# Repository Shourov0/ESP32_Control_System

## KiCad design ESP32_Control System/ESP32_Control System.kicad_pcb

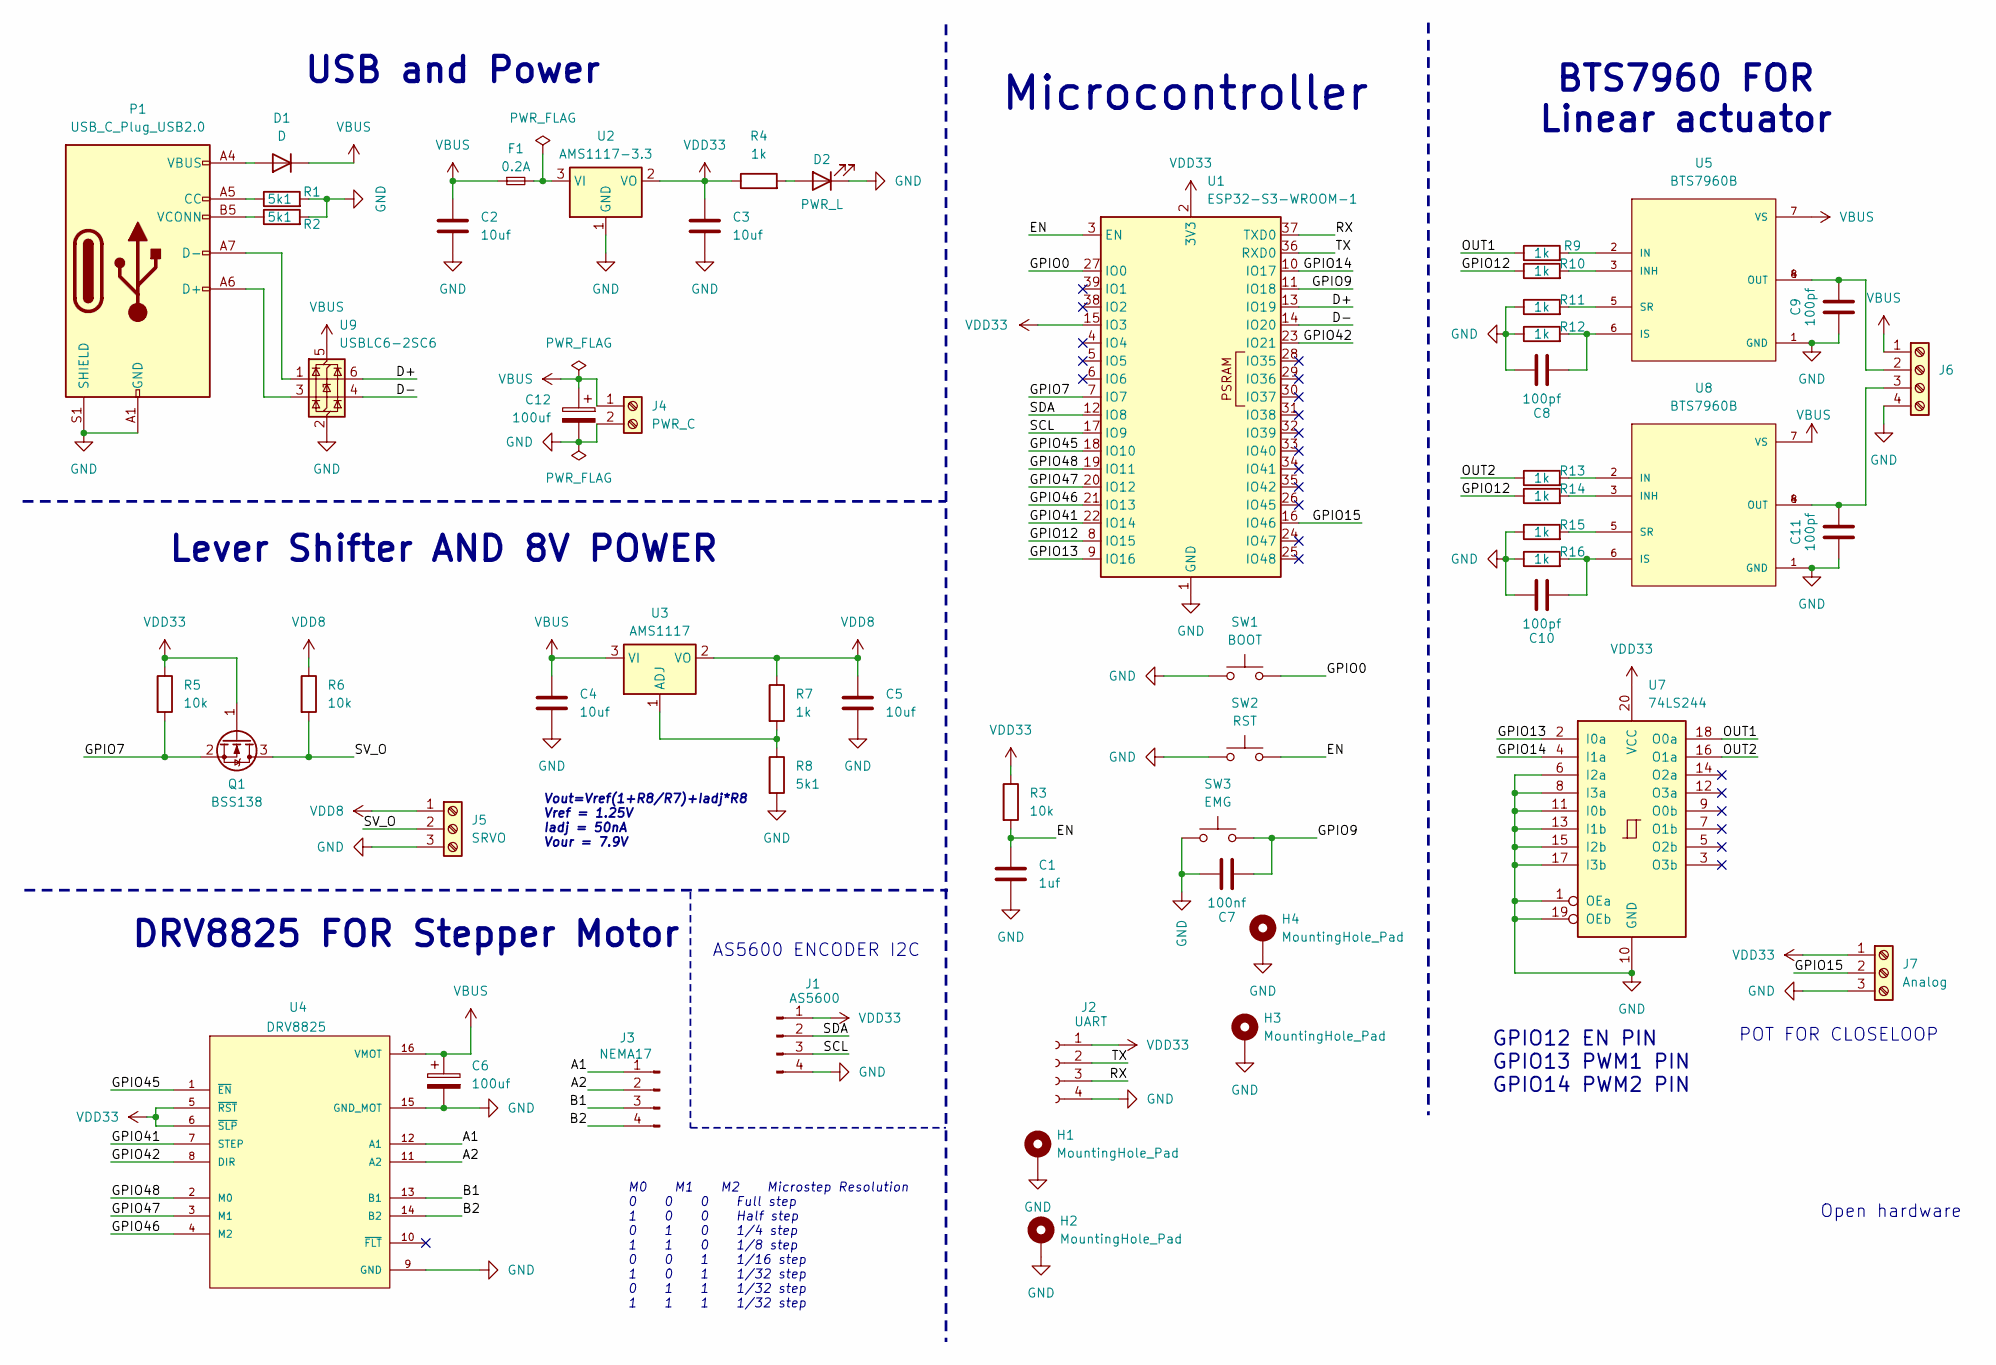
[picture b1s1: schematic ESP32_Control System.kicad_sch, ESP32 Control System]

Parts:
C1: 1uf; C_0402_1005Metric_Pad0.74x0.62mm_HandSolder
C2, C3, C4, C5: 10uf; C_1206_3216Metric_Pad1.33x1.80mm_HandSolder
C6, C12: 100uf; CP_Elec_4x5.8
C7: 100nf; C_0402_1005Metric_Pad0.74x0.62mm_HandSolder
C8, C9, C10, C11: 100pf; C_0402_1005Metric_Pad0.74x0.62mm_HandSolder
D1: D; D_0805_2012Metric_Pad1.15x1.40mm_HandSolder
D2: PWR_L; LED_0805_2012Metric_Pad1.15x1.40mm_HandSolder
F1: 0.2A; Fuse_1206_3216Metric_Pad1.42x1.75mm_HandSolder
H1, H2, H3, H4: MountingHole_Pad; MountingHole_2.5mm_Pad_Via
J1: AS5600; JST_PH_S4B-PH-K_1x04_P2.00mm_Horizontal
J2: UART; PinSocket_1x04_P2.00mm_Vertical_SMD_Pin1Left
J3: NEMA17; JST_PH_S4B-PH-K_1x04_P2.00mm_Horizontal
J4: PWR_C; TerminalBlock_Phoenix_MKDS-3-2-5.08_1x02_P5.08mm_Horizontal
J5: SRVO; JST_PH_S3B-PH-K_1x03_P2.00mm_Horizontal
J6: Screw_Terminal_01x04; TerminalBlock_Phoenix_MKDS-3-4-5.08_1x04_P5.08mm_Horizontal
J7: Analog; JST_PH_S3B-PH-K_1x03_P2.00mm_Horizontal
P1: USB_C_Plug_USB2.0; USB_C_Receptacle_GCT_USB4105-xx-A_16P_TopMnt_Horizontal
Q1: BSS138; SOT-23
R1, R2, R8: 5k1; R_0402_1005Metric_Pad0.72x0.64mm_HandSolder
R3, R5, R6: 10k; R_0402_1005Metric_Pad0.72x0.64mm_HandSolder
R4, R7, R9, R10, R11, R12, R13, R14, R15, R16: 1k; R_0402_1005Metric_Pad0.72x0.64mm_HandSolder
SW1: BOOT; SW_SPST_B3U-1000P
SW2: RST; SW_SPST_B3U-1000P
SW3: EMG; SW_SPST_PTS645
U1: ESP32-S3-WROOM-1
U2: AMS1117-3.3; SOT-223-3_TabPin2
U3: AMS1117; SOT-223-3_TabPin2
U4: DRV8825; IC_DRV8825_STEPPER_MOTOR_DRIVER_CARRIER
U5, U8: BTS7960B; DPAK127P1490X440-8N; PARTREV 1.1
U7: 74LS244; SSOP-20_4.4x6.5mm_P0.65mm
U9: USBLC6-2SC6; SOT-23-6

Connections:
/A1: J3.1, U4.12 (A1)
/A2: J3.2, U4.11 (A2)
/B1: J3.3, U4.13 (B1)
/B2: J3.4, U4.14 (B2)
/D+: U1.13 (IO19), U9.6 (I/O1)
/D-: U1.14 (IO20), U9.4 (I/O2)
/EN: C1.1, R3.2, SW2.2, U1.3 (EN)
/GPIO0: SW1.2, U1.27 (IO0)
/GPIO7: Q1.2 (S), R5.2, U1.7 (IO7)
/GPIO9: C7.2, SW3.2, U1.11 (IO18)
/GPIO12: R10.1, R14.1, U1.8 (IO15)
/GPIO13: U1.9 (IO16), U7.2 (I0a)
/GPIO14: U1.10 (IO17), U7.4 (I1a)
/GPIO15: J7.2, U1.16 (IO46)
/GPIO41: U1.22 (IO14), U4.7 (STEP)
/GPIO42: U1.23 (IO21), U4.8 (DIR)
/GPIO45: U1.18 (IO10), U4.1 (~EN)
/GPIO46: U1.21 (IO13), U4.4 (M2)
/GPIO47: U1.20 (IO12), U4.3 (M1)
/GPIO48: U1.19 (IO11), U4.2 (M0)
/OUT1: R9.1, U7.18 (O0a)
/OUT2: R13.1, U7.16 (O1a)
/RX: J2.3, U1.37 (TXD0)
/SCL: J1.3, U1.17 (IO9)
/SDA: J1.2, U1.12 (IO8)
/SV_O: J5.2, Q1.3 (D), R6.2
/TX: J2.2, U1.36 (RXD0)
GND: C1.2, C2.2, C3.2, C4.2, C5.2, C6.2, C7.1, C8.1, C9.2, C10.1, C11.2, C12.2, D2.1 (K), H1.1, H2.1, H3.1, H4.1, J1.4, J2.4, J4.2, J5.3, J6.4, J7.3, P1.A1 (GND), P1.A12 (GND), P1.B1 (GND), P1.B12 (GND), P1.S1 (SHIELD), R1.2, R2.2, R8.2, R11.1, R12.1, R15.1, R16.1, SW1.1, SW2.1, SW3.1, U1.1 (GND), U1.40 (GND), U1.41 (GND), U2.1 (GND), U4.9 (GND), U4.15 (GND_MOT), U5.1 (GND), U7.1 (OEa), U7.6 (I2a), U7.8 (I3a), U7.10 (GND), U7.11 (I0b), U7.13 (I1b), U7.15 (I2b), U7.17 (I3b), U7.19 (OEb), U8.1 (GND), U9.2 (GND)
unnamed: D1.2 (A), P1.A4 (VBUS), P1.A9 (VBUS), P1.B4 (VBUS), P1.B9 (VBUS)
unnamed: D2.2 (A), R4.2
unnamed: C9.1, J6.2, U5.4 (OUT), U5.8 (OUT)
unnamed: C11.1, J6.3, U8.4 (OUT), U8.8 (OUT)
unnamed: P1.A5 (CC), R1.1
unnamed: P1.A6 (D+), U9.3 (I/O2)
unnamed: P1.A7 (D-), U9.1 (I/O1)
unnamed: P1.B5 (VCONN), R2.1
unnamed: F1.2, U2.3 (VI)
unnamed: R7.2, R8.1, U3.1 (ADJ)
unnamed: R9.2, U5.2 (IN)
unnamed: R10.2, U5.3 (INH)
unnamed: C8.2, R12.2, U5.6 (IS)
unnamed: R11.2, U5.5 (SR)
unnamed: R13.2, U8.2 (IN)
unnamed: R14.2, U8.3 (INH)
unnamed: C10.2, R16.2, U8.6 (IS)
unnamed: R15.2, U8.5 (SR)
VBUS: C2.1, C4.1, C6.1, C12.1, D1.1 (K), F1.1, J4.1, J6.1, U3.3 (VI), U4.16 (VMOT), U5.7 (VS), U8.7 (VS), U9.5 (VBUS)
VDD8: C5.1, J5.1, R6.1, R7.1, U3.2 (VO)
VDD33: C3.1, J1.1, J2.1, J7.1, Q1.1 (G), R3.1, R4.1, R5.1, U1.2 (3V3), U1.15 (IO3), U2.2 (VO), U4.5 (~RST), U4.6 (~SLP), U7.20 (VCC)

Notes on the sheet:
M0 M1 M2 Microstep Resolution 0 0 0 Full step 1 0 0 Half step 0 1 0 1/4 step 1 1 0 1/8 step 0 0 1 1/16 step 1 0 1 1/32 step 0 1 1 1/32 step 1 1 1 1/32 step
AS5600 ENCODER I2C
GPIO12 EN PIN GPIO13 PWM1 PIN GPIO14 PWM2 PIN
USB and Power
Open hardware
Lever Shifter AND 8V POWER
POT FOR CLOSELOOP
Microcontroller
BTS7960 FOR Linear actuator
Vout=Vref(1+R8/R7)+Iadj*R8 Vref = 1.25V Iadj = 50nA Vour = 7.9V
DRV8825 FOR Stepper Motor

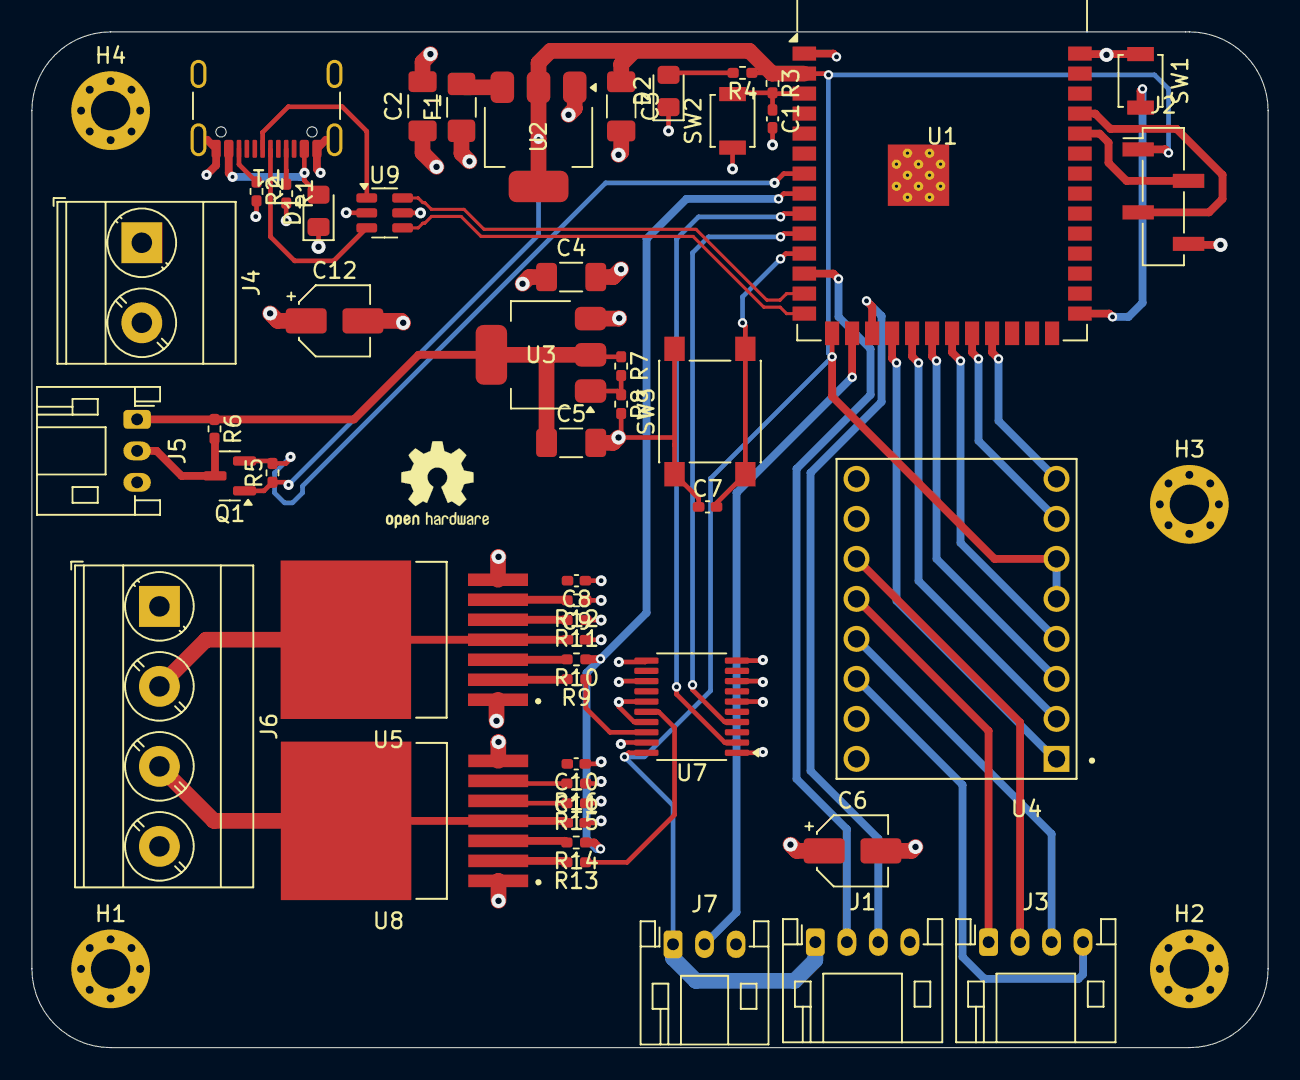
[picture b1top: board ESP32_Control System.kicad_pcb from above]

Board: 4 copper layers, 78.5 x 64.5 mm, 56 parts (0 on the bottom side), 49 nets.

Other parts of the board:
U6: OSHW-Logo2_7.3x6mm_SilkScreen
